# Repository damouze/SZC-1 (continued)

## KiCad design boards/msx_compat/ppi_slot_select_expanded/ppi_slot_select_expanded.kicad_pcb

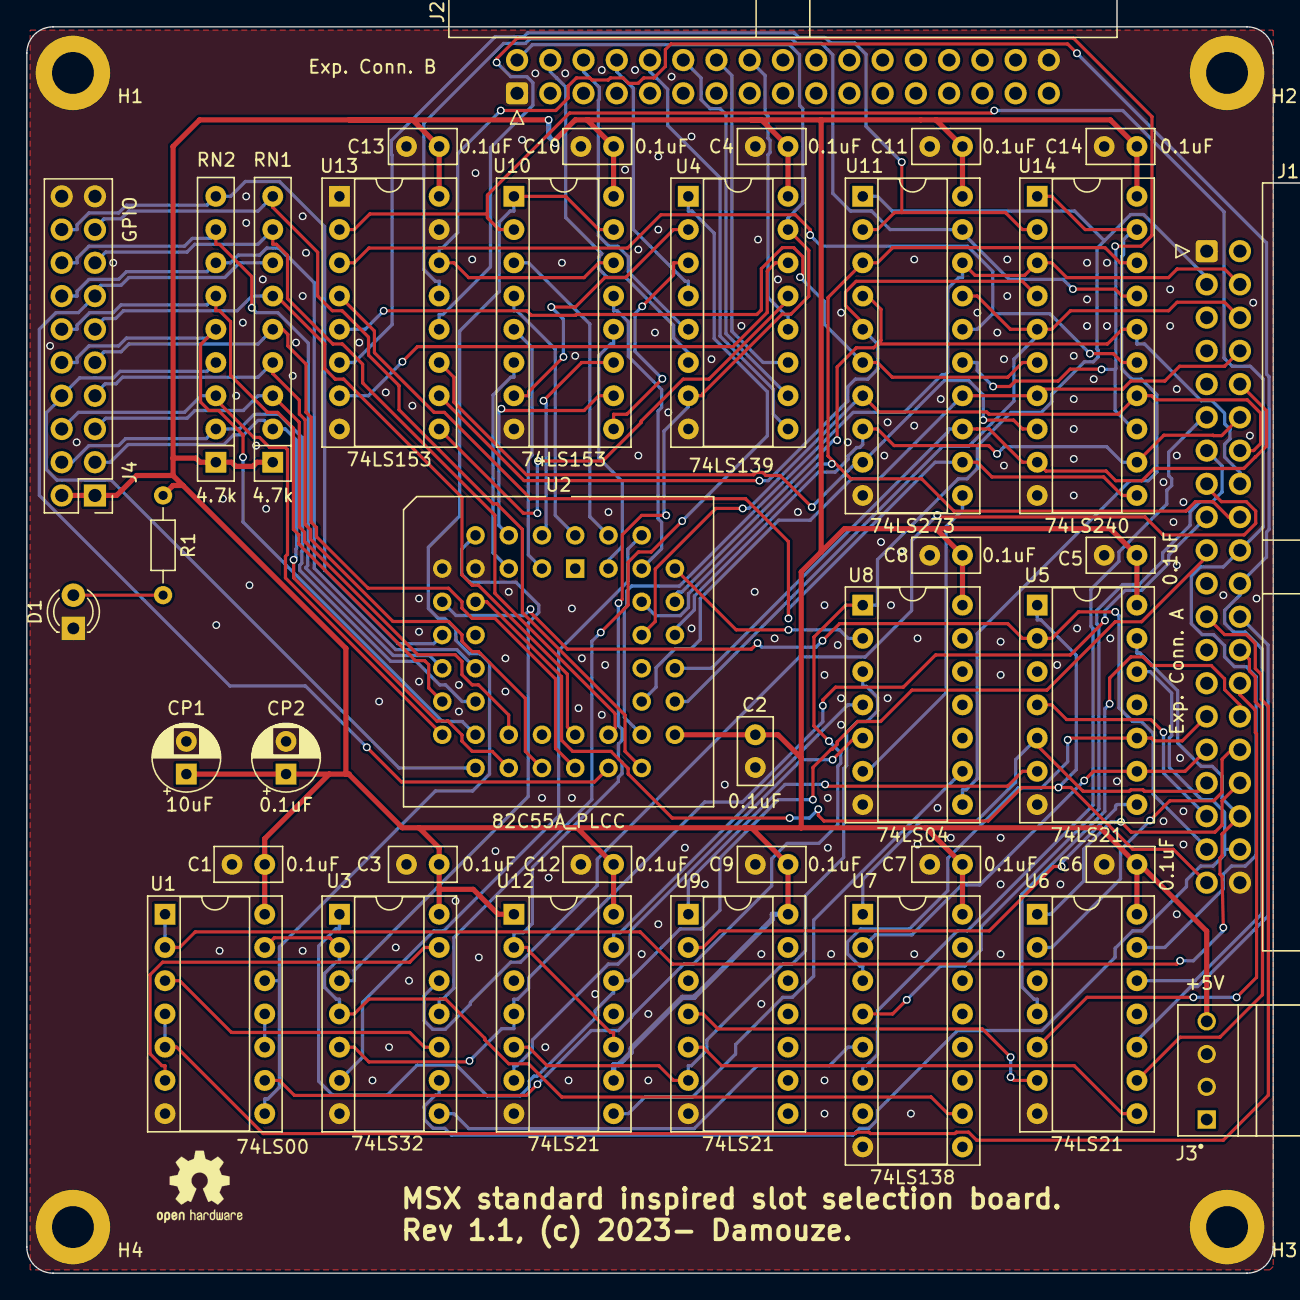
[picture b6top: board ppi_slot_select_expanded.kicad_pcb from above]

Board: 2 copper layers, 95.2 x 95.2 mm, 42 parts (0 on the bottom side), 98 nets.

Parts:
C1, C2, C3, C4, C5, C6, C7, C8, C9, C10, C11, C12, C13, C14: 0.1uF; C_Disc_D5.0mm_W2.5mm_P2.50mm
CP1: 10uF; CP_Radial_D5.0mm_P2.50mm
CP2: 0.1uF; CP_Radial_D5.0mm_P2.50mm
D1: PWR_LED; LED_D3.0mm
H1, H2, H3, H4: MountingHole_Pad; MountingHole_3.2mm_M3_ISO7380_Pad
J1: Exp. Conn. A; IDC-Header_2x20_P2.54mm_Horizontal
J2: Exp. Conn. B; IDC-Header_2x17_P2.54mm_Horizontal
J3: Power; TE_171826-4
J4: GPIO; PinHeader_2x10_P2.54mm_Vertical
R1: 470; R_Axial_DIN0204_L3.6mm_D1.6mm_P7.62mm_Horizontal
RN1, RN2: 4.7k; R_Array_SIP9
U1: 74LS00; DIP-14_W7.62mm_Socket
U2: 82C55A_PLCC; PLCC-44_THT-Socket
U3: 74LS32; DIP-14_W7.62mm_Socket
U4: 74LS139; DIP-16_W7.62mm_Socket
U5, U6, U9, U12: 74LS21; DIP-14_W7.62mm_Socket
U7: 74LS138; DIP-16_W7.62mm_Socket
U8: 74LS04; DIP-14_W7.62mm_Socket
U10, U13: 74LS153; DIP-16_W7.62mm_Socket
U11: 74LS273; DIP-20_W7.62mm_Socket
U14: 74LS240; DIP-20_W7.62mm_Socket

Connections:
/#FFFF: U8.3, U9.6, U12.5
/+5V: C1.1, C2.1, C3.1, C4.1, C5.1, C6.1, C7.1, C8.1, C9.1, C10.1, C11.1, C12.1, C13.1, C14.1, CP1.1, CP2.1, J3.4, J4.1, J4.2, R1.1, RN1.1 (common), RN2.1 (common), U1.14 (VCC), U2.29 (VCC), U3.14 (VCC), U4.16 (VCC), U5.14 (VCC), U6.14 (VCC), U7.16 (VCC), U8.14 (VCC), U9.14 (VCC), U10.16 (VCC), U11.20 (VCC), U12.1, U12.9, U12.14 (VCC), U13.16 (VCC), U14.20 (VCC)
/B_A0: J1.39, U2.10 (A0), U5.1
/B_A1: J1.37, U2.9 (A1), U5.2
/B_A2: J1.35, U5.4
/B_A3: J1.33, U5.5, U7.1 (A0)
/B_A4: J1.31, U5.9, U7.2 (A1)
/B_A5: J1.29, U5.10, U7.3 (A2)
/B_A6: J1.38, U3.9, U5.12
/B_A7: J1.36, U1.1, U1.2, U5.13
/B_A8: J1.34, U6.1
/B_A9: J1.32, U6.2
/B_A10: J1.30, U6.4
/B_A11: J1.28, U6.5
/B_A12: J1.26, U6.9
/B_A13: J1.24, U6.10
/B_A14: J1.22, U6.12, U10.14 (S0), U13.14 (S0)
/B_A15: J1.20, U6.13, U10.2 (S1), U13.2 (S1)
/B_D0: J1.18, U2.38 (D0), U11.3 (D0), U14.18 (O0a)
/B_D1: J1.16, U2.37 (D1), U11.4 (D1), U14.16 (O1a)
/B_D2: J1.14, U2.36 (D2), U11.7 (D2), U14.14 (O2a)
/B_D3: J1.12, U2.35 (D3), U11.8 (D3), U14.12 (O3a)
/B_D4: J1.10, U2.33 (D4), U11.13 (D4), U14.9 (O0b)
/B_D5: J1.8, U2.32 (D5), U11.14 (D5), U14.7 (O1b)
/B_D6: J1.6, U2.31 (D6), U11.17 (D6), U14.5 (O2b)
/B_D7: J1.4, U2.30 (D7), U11.18 (D7), U14.3 (O3b)
/GND: C1.2, C2.2, C3.2, C4.2, C5.2, C6.2, C7.2, C8.2, C9.2, C10.2, C11.2, C12.2, C13.2, C14.2, CP1.2, CP2.2, D1.1 (K), H1.1, H2.1, H3.1, H4.1, J1.1, J1.40, J2.1, J2.34, J3.2, J3.3, J4.19, J4.20, U1.7 (GND), U2.7 (~CS), U2.8 (GND), U3.7 (GND), U4.8 (GND), U5.7 (GND), U6.7 (GND), U7.8 (GND), U8.7 (GND), U9.7 (GND), U10.8 (GND), U11.10 (GND), U12.7 (GND), U13.1 (Ea), U13.8 (GND), U13.15 (Eb), U14.10 (GND)
/PB0: J4.3, RN1.2 (R1), U2.20 (PB0)
/PB1: J4.5, RN1.3 (R2), U2.21 (PB1)
/PB2: J4.7, RN1.4 (R3), U2.22 (PB2)
/PB3: J4.9, RN1.5 (R4), U2.24 (PB3)
/PB4: J4.11, RN1.6 (R5), U2.25 (PB4)
/PB5: J4.13, RN1.7 (R6), U2.26 (PB5)
/PB6: J4.15, RN1.8 (R7), U2.27 (PB6)
/PB7: J4.17, RN1.9 (R8), U2.28 (PB7)
/PC0: J4.4, RN2.2 (R1), U2.16 (PC0)
/PC1: J4.6, RN2.3 (R2), U2.17 (PC1)
/PC2: J4.8, RN2.4 (R3), U2.18 (PC2)
/PC3: J4.10, RN2.5 (R4), U2.19 (PC3)
/PC4: J4.12, RN2.6 (R5), U2.15 (PC4)
/PC5: J4.14, RN2.7 (R6), U2.14 (PC5)
/PC6: J4.16, RN2.8 (R7), U2.13 (PC6)
/PC7: J4.18, RN2.9 (R8), U2.11 (PC7)
/RESET: U2.39 (RESET), U8.2
/Y5: U1.13, U3.2, U3.4, U7.10 (O5)
/~#FFFF: U8.4, U12.13
/~B_IORQ: J1.13, U7.4 (E1)
/~B_M1: J1.11, U7.6 (E3)
/~B_MREQ: J1.15, U3.12
/~B_RD: J1.19, U3.1, U12.12
/~B_RFSH: J1.23, U1.4, U1.5
/~B_WR: J1.17, U3.5, U12.4
/~CS0H: U2.4 (PA1), U10.10 (I0b)
/~CS0L: U2.5 (PA0), U10.6 (I0a)
/~CS1H: U2.2 (PA3), U10.11 (I1b)
/~CS1L: U2.3 (PA2), U10.5 (I1a)
/~CS2H: U2.43 (PA5), U10.12 (I2b)
/~CS2L: U2.44 (PA4), U10.4 (I2a)
/~CS3H: U2.41 (PA7), U10.13 (I3b)
/~CS3L: U2.42 (PA6), U10.3 (I3a)
/~PPI_RD: U2.6 (~RD), U3.3
/~PPI_WR: U2.40 (~WR), U3.6
/~RESET: J1.3, U1.9, U8.1, U11.1 (~Mr)
/~SBSLTSL30: J2.16, U4.12 (O0)
/~SBSLTSL31: J2.14, U4.11 (O1)
/~SBSLTSL32: J2.12, U4.10 (O2)
/~SBSLTSL33: J2.10, U4.9 (O3)
/~SLTSL0: J2.8, U4.4 (O0)
/~SLTSL1: J2.6, U4.5 (O1)
/~SLTSL2: J2.4, U4.6 (O2)
/~SLTSL3: J2.2, U4.7 (O3), U4.15 (E), U12.2, U12.10
/~SSCS0H: U11.5 (Q1), U13.10 (I0b), U14.4 (I1a)
/~SSCS0L: U11.2 (Q0), U13.6 (I0a), U14.2 (I0a)
/~SSCS1H: U11.9 (Q3), U13.11 (I1b), U14.8 (I3a)
/~SSCS1L: U11.6 (Q2), U13.5 (I1a), U14.6 (I2a)
/~SSCS2H: U11.15 (Q5), U13.12 (I2b), U14.13 (I1b)
/~SSCS2L: U11.12 (Q4), U13.4 (I2a), U14.11 (I0b)
/~SSCS3H: U11.19 (Q7), U13.13 (I3b), U14.17 (I3b)
/~SSCS3L: U11.16 (Q6), U13.3 (I3a), U14.15 (I2b)
unnamed: D1.2 (A), R1.2
unnamed: U1.3, U3.10
unnamed: U1.6, U3.13
unnamed: U1.10, U1.11
unnamed: U3.11, U4.1 (E)
unnamed: U5.6, U9.1
unnamed: U5.8, U9.2
unnamed: U6.6, U9.4
unnamed: U6.8, U9.5
unnamed: U3.8, U7.5 (E2)
unnamed: U1.8, U1.12, U10.1 (Ea), U10.15 (Eb)
unnamed: U4.2 (A0), U10.7 (Za)
unnamed: U4.3 (A1), U10.9 (Zb)
unnamed: U8.6, U11.11 (Cp)
unnamed: U8.5, U12.6
unnamed: U8.9, U12.8
unnamed: U4.14 (A0), U13.7 (Za)
unnamed: U4.13 (A1), U13.9 (Zb)
unnamed: U8.8, U14.1 (OEa), U14.19 (OEb)
